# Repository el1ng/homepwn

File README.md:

# Homepwn

This repo contains KiCAD projects for a breakout to help jailbreak the homepod.

There are 3 projects:
- homebreakout: This is a form fitting PCB that fits underneath the homepod and contacts the POGO pins
- homepod_usb_breakout: This is a more complex PCB that does UART to USB and provides a USB connection to the Homepod.
- homepod_usb_breakout_simple: This is a simple, through hole, PCB that provides a USB connection to the Homepod, and access to the 1.8V UART pins directly.

You will need homebreakout and either homepod_usb_breakout or homepod_usb_breakout_simple

After soldering homebreakout, verify that the POGO pins do not touch each other. It requires a bit of patience and skill to solder them straight.

(note the image above has one of the FFC connectors backwards)

# 3D print version
Additionally this repo contains a 3D printable adapter, which exposes the connections and can be used for USB.  
Note: UART connections are also exposed, but require an appropriate 1.8V UART to USB controller.  

Additionally you will need M2x6 screws and Pogo pins.
The ones i used have the following properties:
- 1.02 mm outer diameter
- 15.8 mm total length
- 1.4  mm pin length  
(i used these: https://www.amazon.de/dp/B07SKD8Q42)

Print with the side going into the homepod facing upwards and print with support. First solder wires to the pins, only then insert them into the adapter (otherwise the 3D printed plastic will melt). Make sure they have a good solder connection, otherwise the USB connection will be very unstable or will not work at all.

<br>

# Warning

Jailbreaking your Homepod is not supported, and these design files were made from reverse engineering. While they should not cause physical damage to your Homepod assuming they are soldered correctly, you are ultimately responsible for any damage you cause.

Note that no IPSWs are available for the Homepod, and if the Jailbreak fails you will be stuck with a $250 paperweight. Proceed with caution.

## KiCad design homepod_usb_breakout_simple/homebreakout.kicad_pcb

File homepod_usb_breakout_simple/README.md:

# Homepod USB Breakout Simple
This is a simpler version of the USB Breakout. If you do not require UART and/or you want to solder through hole components instead, make this board.
It uses a USB B connector as it is simple to solder.

If you would like to access UART, you can via the pin headers. Note that UART is 1.8V and _NOT_ 3.3V compatible.

# BOM
| MFG | Part        | Qty | DigiKey     | Mouser          |
| --- | ----------- | --- | -------     | ------          |
| CUI | UJ2-BH-2-TH | 1   | 102-5884-ND | 490-UJ2-BH-2-TH |
| FCI | SLW8S-1C7LF | 1   | 609-1935-ND | 649-SLW8S-1C7LF |

1x5 0.1" Pin header

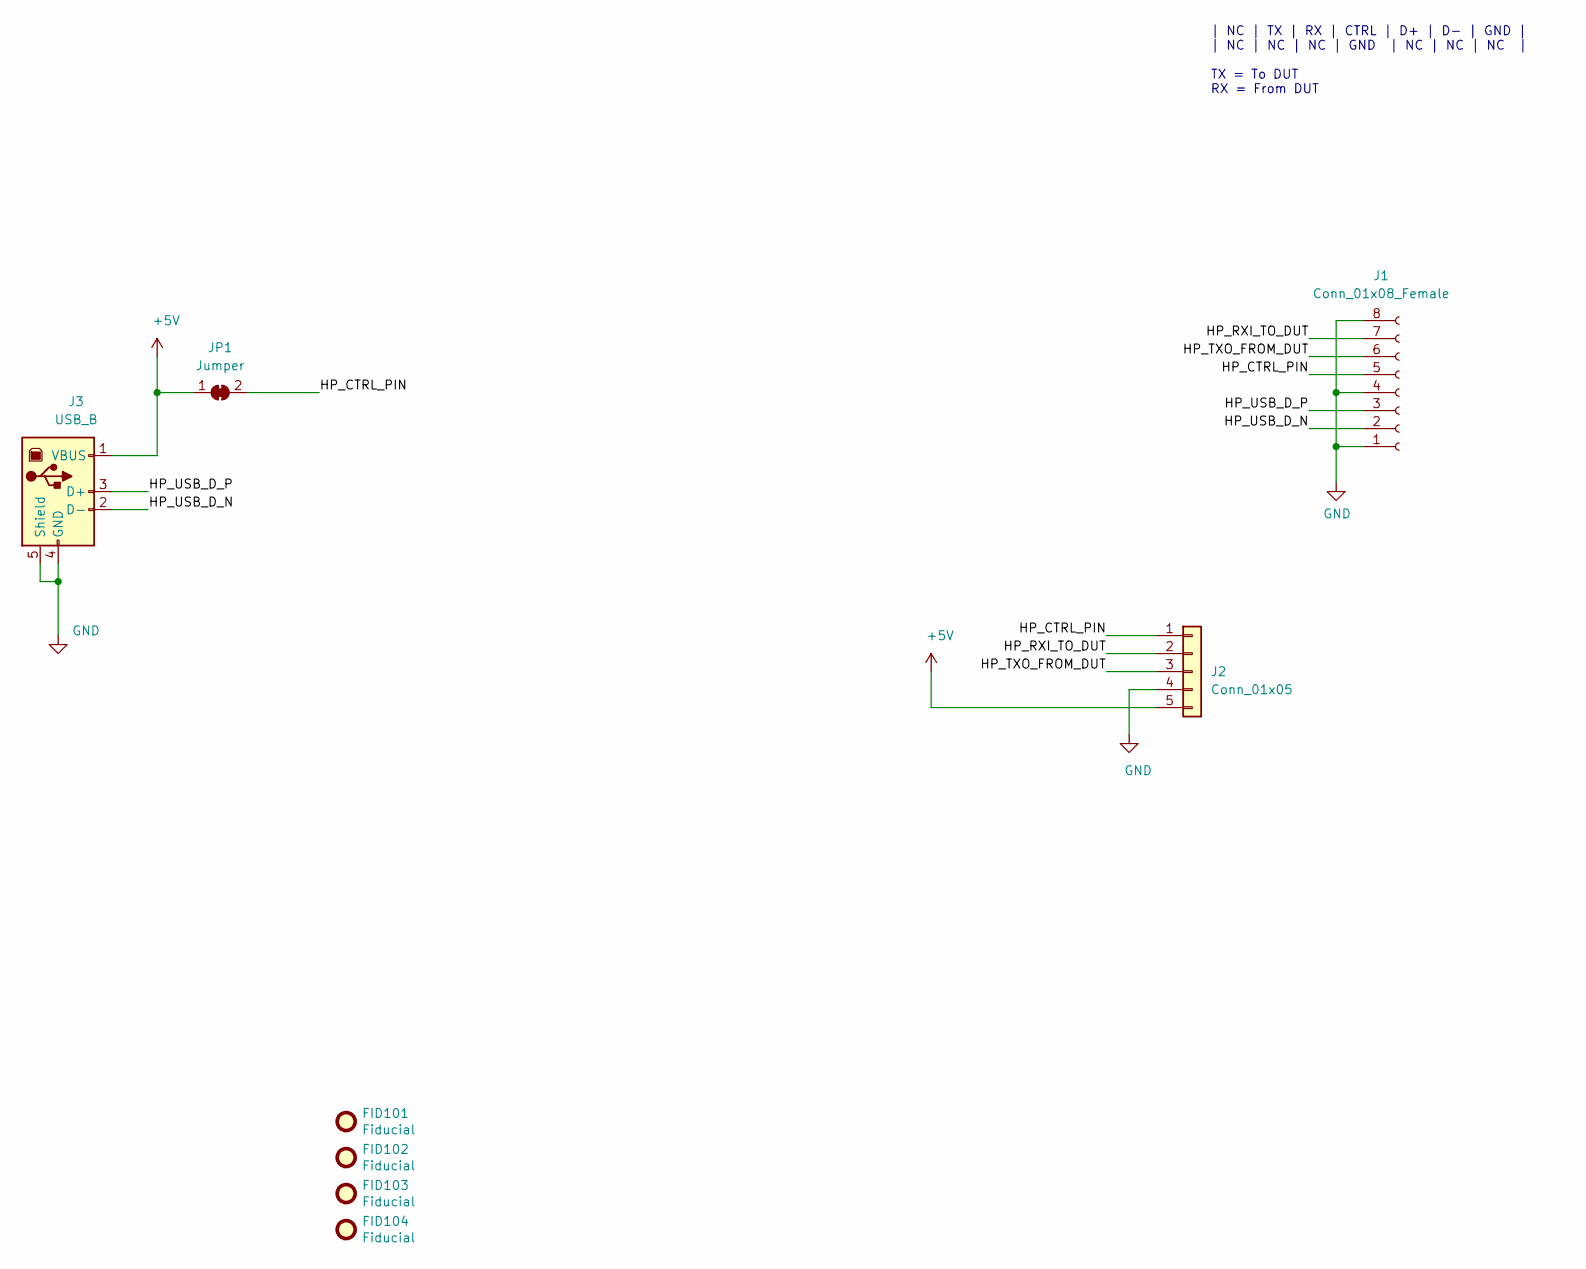
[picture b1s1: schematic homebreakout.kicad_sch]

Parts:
FID101, FID102, FID103, FID104: Fiducial; Fiducial_0.5mm_Dia_1mm_Outer
J1: Conn_01x08_Female; SLW8S-1C7LF
J2: Conn_01x05; PinSocket_1x05_P2.54mm_Vertical
J3: USB_B; USB_B_Lumberg_2411_02_Horizontal
JP1: Jumper; SolderJumper-2_P1.3mm_Bridged_Pad1.0x1.5mm

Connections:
+5V: J2.5, J3.1 (VBUS), JP1.1 (A)
/HP_CTRL_PIN: J1.5, J2.1, JP1.2 (B)
/HP_RXI_TO_DUT: J1.7, J2.2
/HP_TXO_FROM_DUT: J1.6, J2.3
/HP_USB_D_N: J1.2, J3.2 (D-)
/HP_USB_D_P: J1.3, J3.3 (D+)
GND: J1.1, J1.4, J1.8, J2.4, J3.4 (GND), J3.5 (Shield)

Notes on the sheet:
| NC | TX | RX | CTRL | D+ | D- | GND | | NC | NC | NC | GND | NC | NC | NC | TX = To DUT RX = From DUT

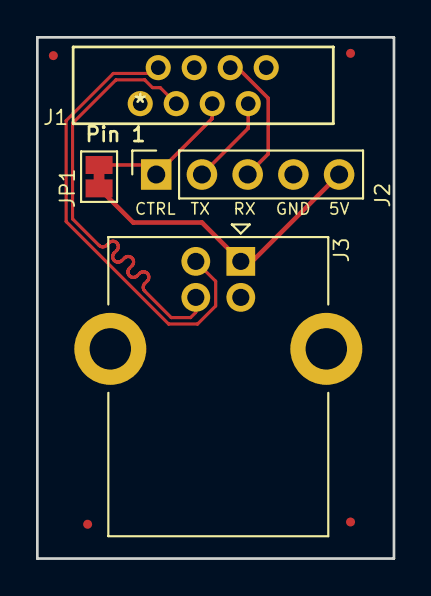
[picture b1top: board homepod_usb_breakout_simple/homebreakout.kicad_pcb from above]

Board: 2 copper layers, 19.8 x 29.0 mm, 8 parts (0 on the bottom side), 7 nets.

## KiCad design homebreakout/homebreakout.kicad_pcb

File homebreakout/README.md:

# Homepod Breakout Connector
This is a form fitting breakout for the bottom of the Homepod. The Homepod bottom connector has the following pinout:

    | NC | TX | RX | CTRL | D+ | D- | GND |
    | NC | NC | NC | GND  | NC | NC | NC  |
    
    TX = UART To Homepod (1.8V)
    RX = UART From Homepod (1.8V)
    NC = No connect

CTRL is a voltage controlled pin. It works as follows:

    | No Connect, 0V up to 1.8V | No Function               |
    | 1.8V to ~3.3V             | UART Enabled              |
    | 3.3 to 5V                 | UART Enabled, USB Enabled |

Unfortunately there does not seem to be additional functionality embedded in the CTRL or other pins. I disassembled multiple Homepods and traced the pins back to the A8 processor and PMIC to verify. There are some non populated components near where the control pin goes by that may have been present during development.

UART is 1.8V. It is most likely _not_ 3.3V compatible.

# DFU Procedure

Flip the Homepod upside down and plug it in. Really.

After it enters DFU mode flip it right side up, or it will re-enter DFU mode. @DanyL has been working on a checkra1n patch to make it not enter DFU mode.

There was a lot of fun reverse engineering to figure out how this works. Might make for a good blog post one day.

# BOM

| MFG    | Part                  | Qty | DigiKey       | Mouser           |
| ---    | -----------           | --- | -------       | ------           |
| FCI    | SLW8S-1C7LF           | 1   | 609-1935-ND   | 649-SLW8S-1C7LF  |
| Harwin | P70-2100045R          | 8   | 952-3134-1-ND | 855-P70-2100045R |
| Any    | M2x5mm machine screws | 4   |               |                  |

You will need an opposite side 8 pin 1mm pitch FFC cable. Such as:
Molex 15167-0236
DigiKey: WM22868-ND
Mouser: 538-15167-0236

You can also get a same side connector and solder the FCI connector reversed. I recommend getting one opposite side and one same side in case you accidentally flip one of the FFC connectors.
You will need 4 M2 machine screws. 3mm to 5mm screws work well.

# Installation

Pogo pins face down, SLW85 connector goes up. The cutouts in the PCB are to help
make sure the pogo pin alignment is correct.

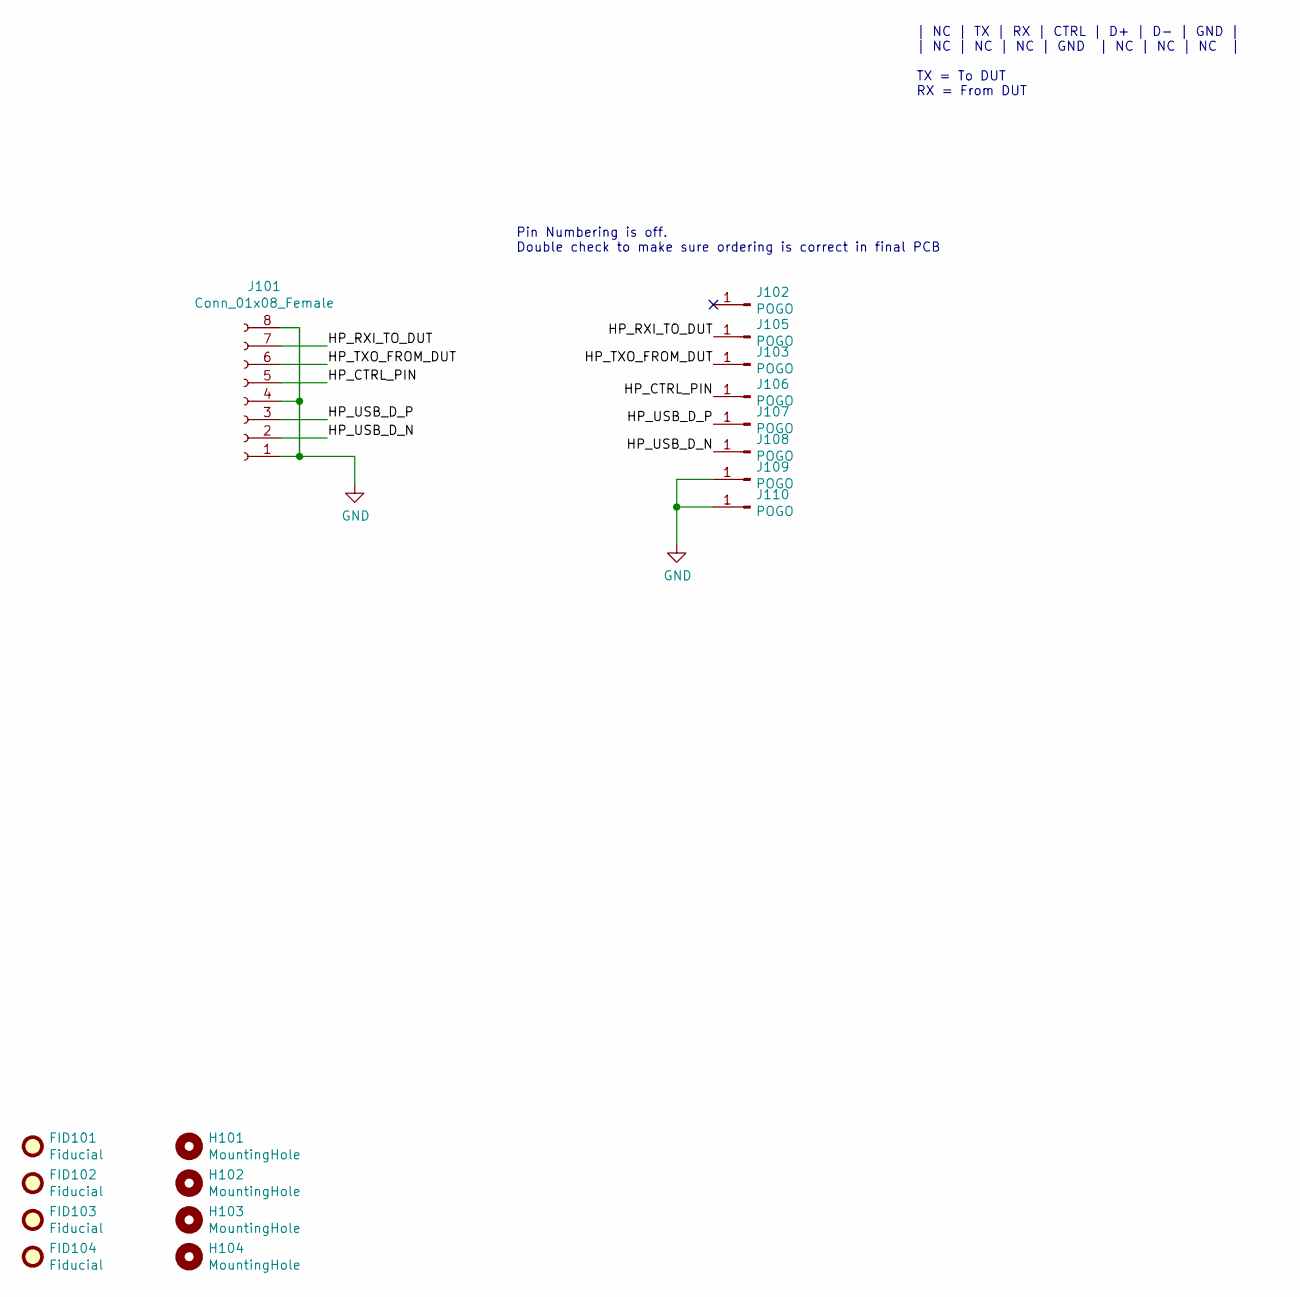
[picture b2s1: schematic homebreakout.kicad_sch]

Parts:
FID101, FID102, FID103, FID104: Fiducial; Fiducial_0.5mm_Dia_1mm_Outer
H101, H102, H103, H104: MountingHole; MountingHole_2.2mm_M2
J101: Conn_01x08_Female; SLW8S-1C7LF
J102, J103, J105, J106, J107, J108, J109, J110: POGO; P70_POGO

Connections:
/HP_CTRL_PIN: J101.5, J106.1
/HP_RXI_TO_DUT: J101.7, J105.1
/HP_TXO_FROM_DUT: J101.6, J103.1
/HP_USB_D_N: J101.2, J108.1
/HP_USB_D_P: J101.3, J107.1
GND: J101.1, J101.4, J101.8, J109.1, J110.1

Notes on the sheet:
Pin Numbering is off. Double check to make sure ordering is correct in final PCB
| NC | TX | RX | CTRL | D+ | D- | GND | | NC | NC | NC | GND | NC | NC | NC | TX = To DUT RX = From DUT

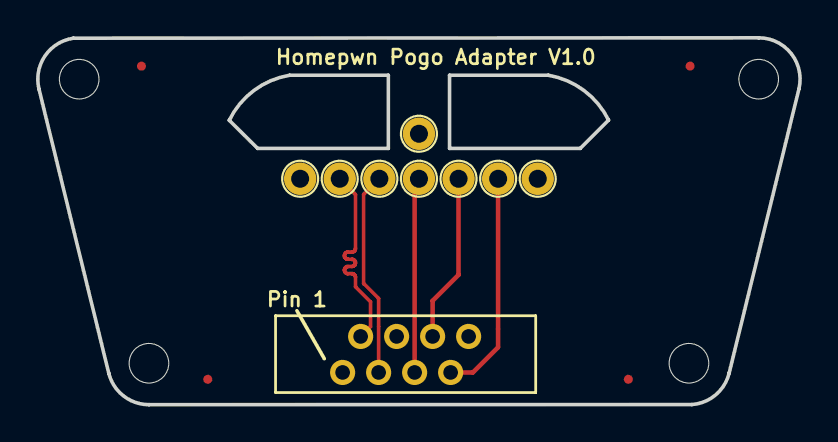
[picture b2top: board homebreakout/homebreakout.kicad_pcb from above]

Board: 2 copper layers, 42.3 x 20.4 mm, 17 parts (0 on the bottom side), 6 nets.

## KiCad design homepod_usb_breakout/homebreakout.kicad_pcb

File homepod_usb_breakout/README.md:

# Homepod USB Breakout

This USB breakout contains both a USB and UART USB connector.

In theory the UART control extra pins can also change between USB+UART and UART only mode, however, the default configuration both UART+USB are enabled.

# BOM

| Id | Designator     | Quantity | Designation       | MFG        | Part             | DigiKey               | Mouser               |
| -- | -------------- | -------- | ----------------- | ---------- | ---------------- | --------------------- | -------------------- |
| 1  | J101,J102      | 2        | USB_B_Micro       | FCI        | 10118193-0001LF  | 609-4616-1-ND         | 649-10118193-0001LF  |
| 2  | U103           | 1        | TPS22948DCKR      | TI         | TPS22948DCKR     | 595-TPS22948DCKR      | 595-TPS22948DCKR     |
| 3  | D101,D102,D103 | 3        | BAT48JFILM        | Infineon   | BAT60AE6327HTSA1 | BAT60AE6327HTSA1CT-ND | 726-BAT60AE6327HTSA1 |
| 4  | C106,C104,C105 | 3        | 100nF             | Any        | Eg               | 311-1366-1-ND         | 603-C0603MRY5V9BB104 |
| 5  | R101,R102      | 2        | 27                | Any        | Eg               | 311-27GRCT-ND         | 603-RC0603JR-0727RL  |
| 6  | C101,C103,C107 | 3        | 1uF               | Any        | Eg               | 3490-1550-1-ND        | 81-GRM39R105K6.3     |
| 7  | C102           | 1        | 10uF              | Any        | Eg               | 478-10766-1-ND        | 581-0603ZD106KAT2A   |
| 8  | R103,R104      | 2        | 10k               | Any        | Eg               | MCT0603-10K-MDCT-ND   | 594-MCT0603MD1002DP5 |
| 9  | U101           | 1        | AP2127K-1.8       | Diodes Inc | AP2127K-1.8TRG1  | AP2127K-1.8TRG1       | 621-AP2127K-1.8TRG1  |
| 10 | U102           | 1        | FT230XS           | FTDI       | FT230XS-R        | 895-FT230XS-R         | 895-FT230XS-R        |
| 11 | J1             | 1        | Conn_01x08_Female | FCI        | SLW8S-1C7LF      | 609-1935-ND           | 649-SLW8S-1C7LF      |
| 12 | J2             | 1        | Conn_01x04        | Any        | Eg               | 732-5317-ND           | 710-61300411121      |
| 13 | J3             | 1        | Conn_01x03_Male   | Any        | Eg               | 732-5316-ND           | 710-61300311121      |

Don't forget an _opposite_ sided 8pin 1mm FFC cable

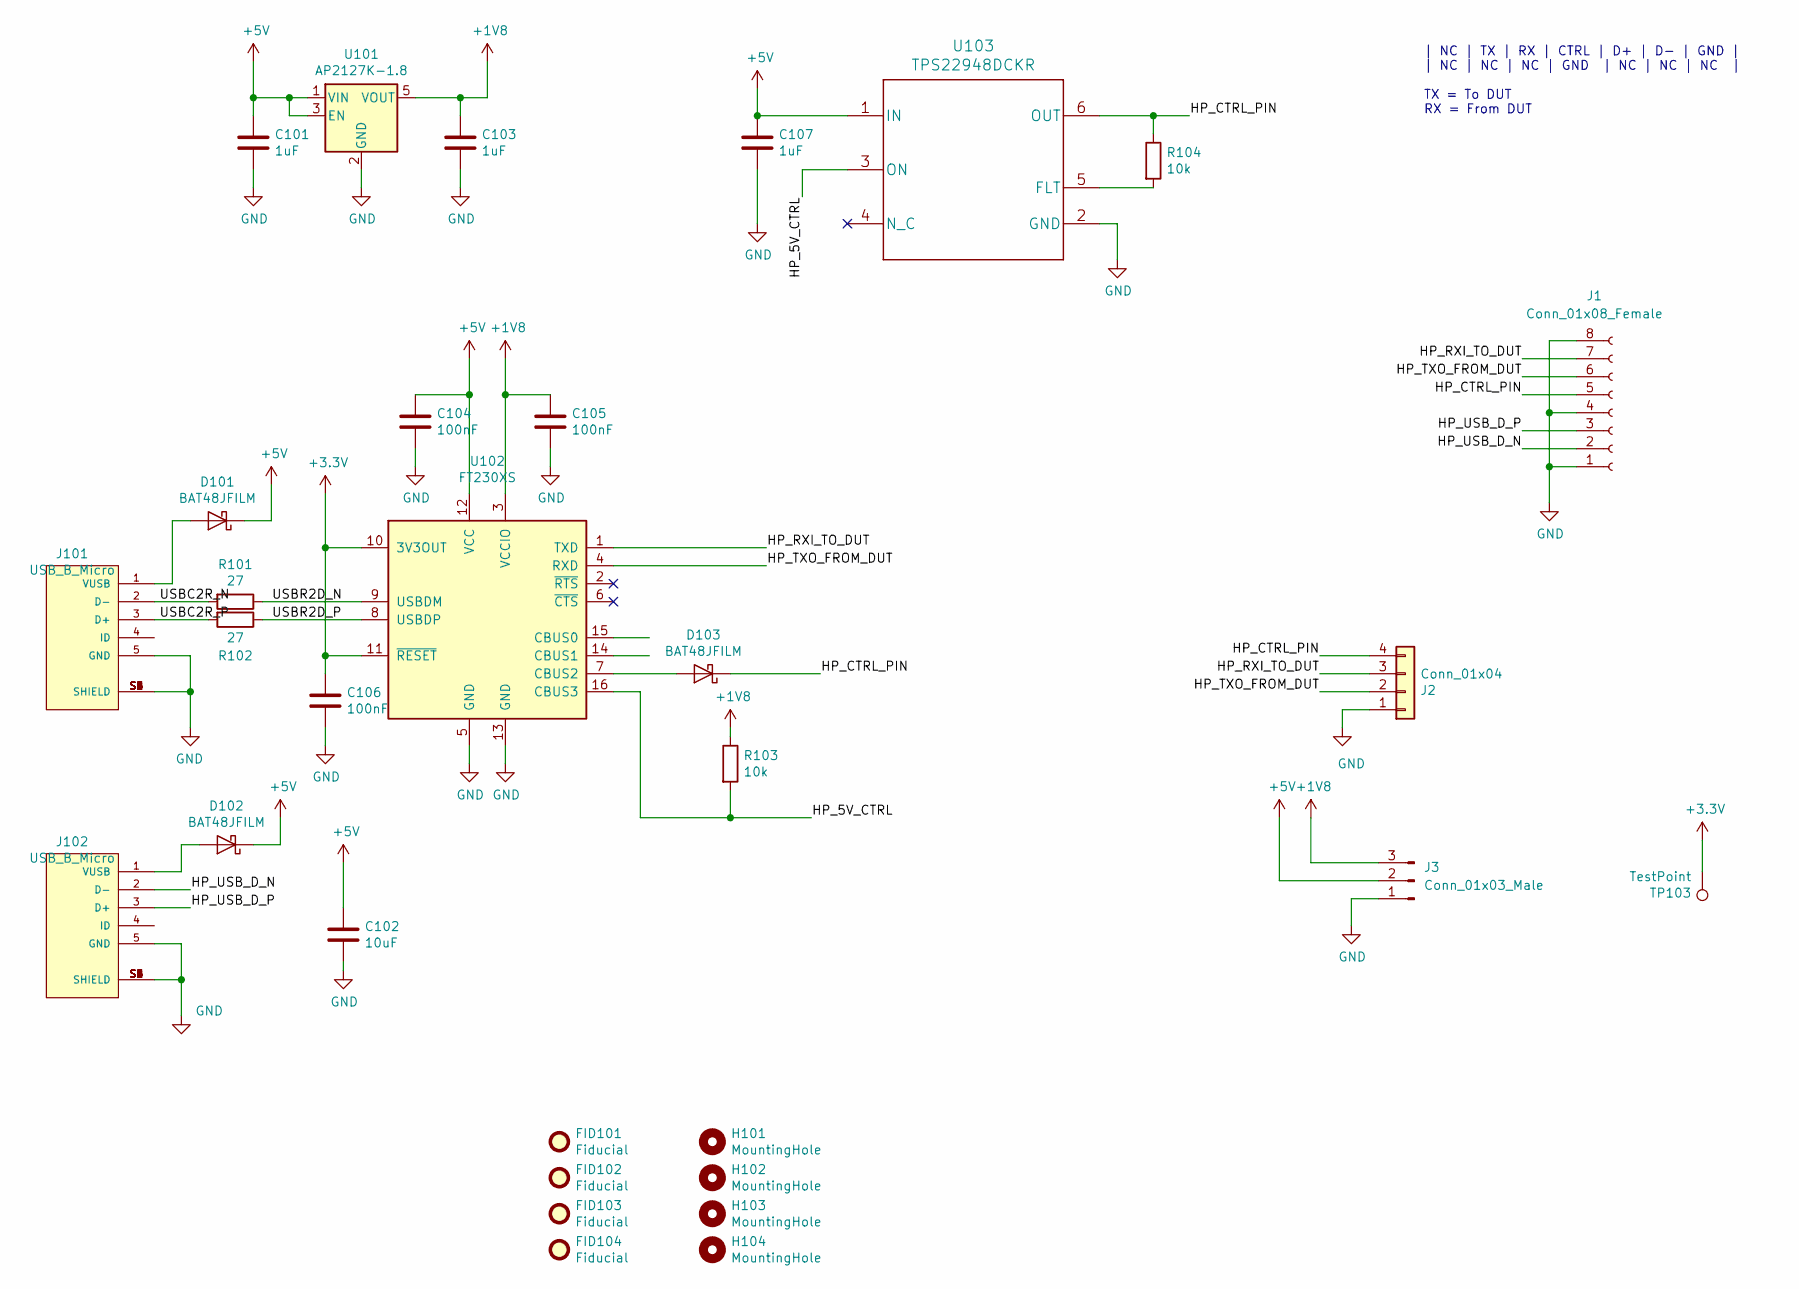
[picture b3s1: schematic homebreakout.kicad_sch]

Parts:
C101, C103, C107: 1uF; C_0603_1608Metric
C102: 10uF; C_0603_1608Metric
C104, C105, C106: 100nF; C_0603_1608Metric
D101, D102, D103: BAT48JFILM; D_SOD-323_HandSoldering
FID101, FID102, FID103, FID104: Fiducial; Fiducial_0.5mm_Dia_1mm_Outer
H101, H102, H103, H104: MountingHole; MountingHole_2.2mm_M2
J1: Conn_01x08_Female; SLW8S-1C7LF
J2: Conn_01x04; PinHeader_1x04_P2.54mm_Vertical
J3: Conn_01x03_Male; PinHeader_1x03_P2.54mm_Vertical
J101, J102: USB_B_Micro; FCI_10118193-0001LF
R101, R102: 27; R_0603_1608Metric
R103, R104: 10k; R_0603_1608Metric
TP103: TestPoint; TestPoint_Pad_D1.0mm
U101: AP2127K-1.8; SOT-23-5_HandSoldering
U102: FT230XS; SSOP-16_3.9x4.9mm_P0.635mm
U103: TPS22948DCKR; SOT-363_SC-70-6_Handsoldering

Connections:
+1V8: C103.1, C105.1, J3.3, R103.1, U101.5 (VOUT), U102.3 (VCCIO)
+3V3: C106.1, TP103.1, U102.10 (3V3OUT), U102.11 (~RESET)
+5V: C101.1, C102.1, C104.1, C107.1, D101.1 (K), D102.1 (K), J3.2, U101.1 (VIN), U101.3 (EN), U102.12 (VCC), U103.1 (IN)
/HP_5V_CTRL: R103.2, U102.16 (CBUS3), U103.3 (ON)
/HP_CTRL_PIN: D103.1 (K), J1.5, J2.4, R104.1, U103.6 (OUT)
/HP_RXI_TO_DUT: J1.7, J2.3, U102.1 (TXD)
/HP_TXO_FROM_DUT: J1.6, J2.2, U102.4 (RXD)
/HP_USB_D_N: J1.2, J102.2 (D-)
/HP_USB_D_P: J1.3, J102.3 (D+)
/USBC2R_N: J101.2 (D-), R101.2
/USBC2R_P: J101.3 (D+), R102.2
/USBR2D_N: R101.1, U102.9 (USBDM)
/USBR2D_P: R102.1, U102.8 (USBDP)
GND: C101.2, C102.2, C103.2, C104.2, C105.2, C106.2, C107.2, J1.1, J1.4, J1.8, J2.1, J3.1, J101.5 (GND), J101.S1 (SHIELD), J101.S2 (SHIELD), J101.S3 (SHIELD), J101.S4 (SHIELD), J101.S5 (SHIELD), J101.S6 (SHIELD), J102.5 (GND), J102.S1 (SHIELD), J102.S2 (SHIELD), J102.S3 (SHIELD), J102.S4 (SHIELD), J102.S5 (SHIELD), J102.S6 (SHIELD), U101.2 (GND), U102.5 (GND), U102.13 (GND), U103.2 (GND)
unnamed: D101.2 (A), J101.1 (VUSB)
unnamed: D102.2 (A), J102.1 (VUSB)
unnamed: D103.2 (A), U102.7 (CBUS2)
unnamed: R104.2, U103.5 (FLT)

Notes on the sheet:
| NC | TX | RX | CTRL | D+ | D- | GND | | NC | NC | NC | GND | NC | NC | NC | TX = To DUT RX = From DUT

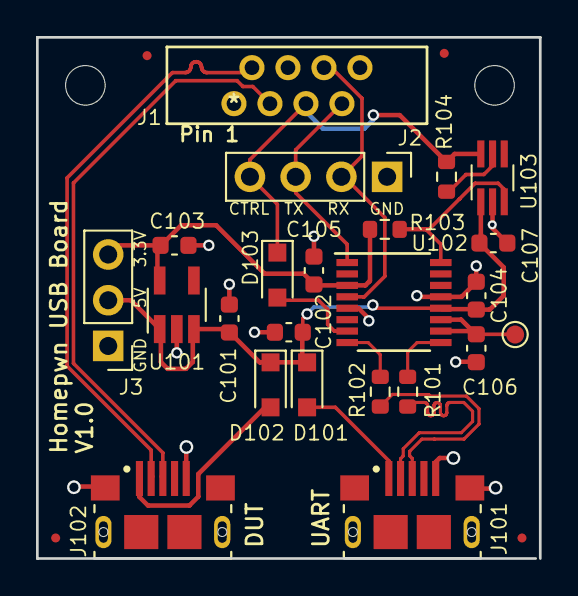
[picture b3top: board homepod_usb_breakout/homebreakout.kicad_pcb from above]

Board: 2 copper layers, 27.9 x 29.0 mm, 29 parts (0 on the bottom side), 18 nets.

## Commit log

2021-03-23 Homepwn V1.0
2023-02-20 add 3d print version
2023-02-20 add images
2023-02-20 make homepod insert a bit shorter so that the pogo pins don't press too hard into the pads
